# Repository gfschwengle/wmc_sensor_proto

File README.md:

# wmc_sensor_proto
This repo contains everyhting about the project:
- PCB_design: KiCad board design
- firmware: PlatformIO firmware design
- docs: datasheet and images

Still to do;
1. Calibrate the sensor, use a reference sensor. (not tested, atm no reference sensor).
2. Test the system MQTT, to communicate with a raspberry PI (not tested)
3. SD card read and write (Tested, failed)

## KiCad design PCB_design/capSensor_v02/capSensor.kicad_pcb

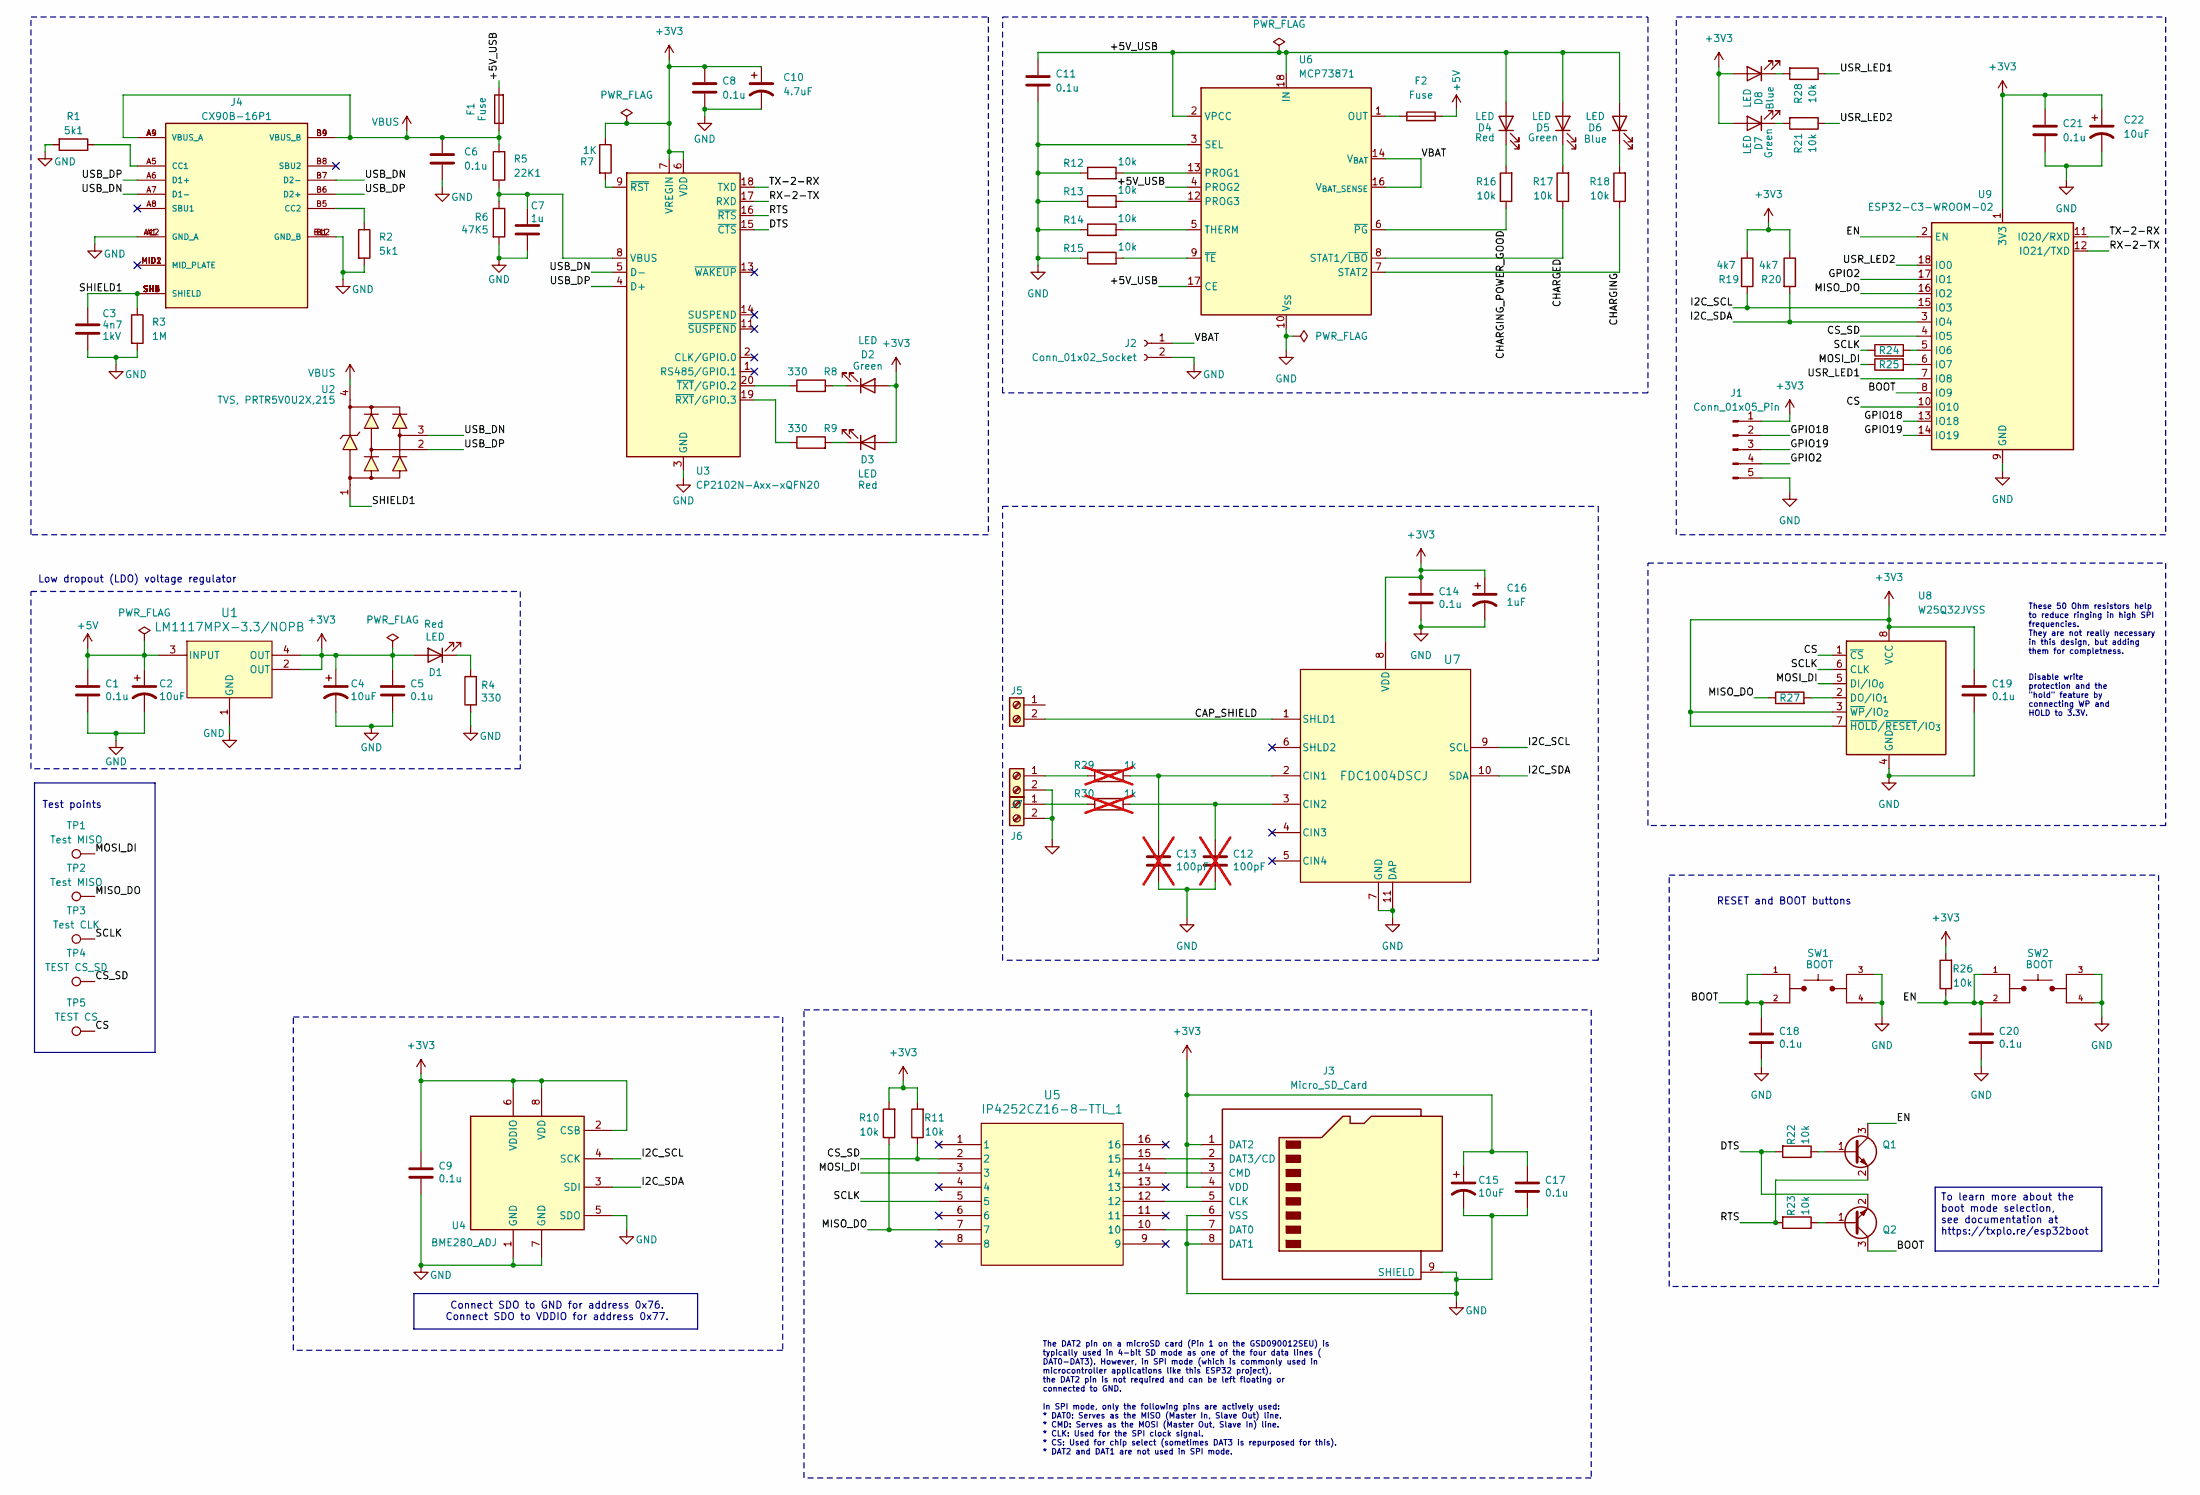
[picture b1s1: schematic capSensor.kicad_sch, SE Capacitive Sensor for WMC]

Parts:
C1, C5, C6, C8, C9, C11, C14, C17, C18, C19, C20, C21: 0.1u; C_0805_2012Metric_Pad1.18x1.45mm_HandSolder; MPN C0805C104K4RACAUTO
C2, C4, C15, C22: 10uF; CAPC3216X110N; MPN T491A106K010AT7280
C3: 4n7; C_0805_2012Metric_Pad1.18x1.45mm_HandSolder; MPN C0805C472K5RECAUTO
C7: 1u; C_0805_2012Metric_Pad1.18x1.45mm_HandSolder; Voltage 1kV; Tolerance 100%; MPN C0805C105K4RACTU
C10: 4.7uF; CAPC3216X110N; MPN T491A475K025AT
C12, C13: 100pF; C_0805_2012Metric_Pad1.18x1.45mm_HandSolder; not fitted
C16: 1uF; CAPC3216X110N; MPN T491A105K016AT
D1, D3, D4: LED; LED_0805_2012Metric_Pad1.15x1.40mm_HandSolder; MPN LTST-C170KRKT
D2, D5, D7: LED; LED_0805_2012Metric_Pad1.15x1.40mm_HandSolder; MPN LTST-C170GKT
D6, D8: LED; LED_0805_2012Metric_Pad1.15x1.40mm_HandSolder; MPN LTST-C170TBKT
F1: Fuse; Fuse_1210_3225Metric_Pad1.42x2.65mm_HandSolder; MPN 0ZCH0110AF2E
F2: Fuse; Fuse_0805_2012Metric_Pad1.15x1.40mm_HandSolder; MPN FBMJ2125HM330-T
J1: Conn_01x05_Pin; PinHeader_1x05_P1.00mm_Vertical_SMD_Pin1Left
J2: Conn_01x02_Socket; JST_S2B-PH-SM4-TB; MPN S2B-PH-SM4-TB
J3: Micro_SD_Card; microSD_HC_Wuerth_693072010801; MPN 693072010801
J4: CX90B-16P1; HIROSE_CX90B-16P1; PARTREV 23.04.05
J5, J6, J7: Screw_Terminal_01x02; TerminalBlock_Xinya_XY308-2.54-2P_1x02_P2.54mm_Horizontal
Q1, Q2: BC817; SOT-23; Manufacturer_Part_Number BC817
R1, R2: 5k1; R_0805_2012Metric_Pad1.20x1.40mm_HandSolder; MPN RMCF0805FT5K10
R3: 1M; R_0805_2012Metric_Pad1.20x1.40mm_HandSolder; MPN RMCF0805FT1M00
R4: 330; R_0805_2012Metric; MPN RMCF0805FT330K
R5: 22K1; R_0805_2012Metric_Pad1.20x1.40mm_HandSolder; MPN RMCF0805FT22K1
R6: 47K5; R_0805_2012Metric; MPN RMCF0805FT47K5
R7: 1K; R_0805_2012Metric_Pad1.20x1.40mm_HandSolder; MPN RNCP0805FTD1K00
R8, R9: 330; R_0805_2012Metric_Pad1.20x1.40mm_HandSolder; MPN RMCF0805FT330K
R10, R11, R12, R13, R14, R15, R16, R17, R18, R21, R22, R23, R26, R28: 10k; R_0805_2012Metric_Pad1.20x1.40mm_HandSolder; MPN RMCF0805FT10K0
R19, R20: 4k7; R_0805_2012Metric_Pad1.20x1.40mm_HandSolder; MPN RMCF0805FT4K70
R24, R25, R27: 50; R_0805_2012Metric; MPN CRCW080550R0FKTA
R29, R30: 1k; R_0805_2012Metric_Pad1.20x1.40mm_HandSolder; not fitted
SW1, SW2: SW_TL3305AF260QG; PARTREV C
TP1, TP2: Test MISO; TestPoint_Pad_D1.0mm
TP3: Test CLK; TestPoint_Pad_D1.0mm
TP4: TEST CS_SD; TestPoint_Pad_D1.0mm
TP5: TEST CS; TestPoint_Pad_D1.0mm
U1: LM1117MPX-3.3/NOPB; DCY0004A_M
U2: TVS, PRTR5V0U2X,215; SOT-143; Voltage - reverse Stand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 5.5V; Voltage - breakdown 6V; MPN PRTR5V0U2X,215; LCSC C12333
U3: CP2102N-Axx-xQFN20; SiliconLabs_QFN-20-1EP_3x3mm_P0.5mm_EP1.8x1.8mm; MPN CP2102N-A02-GQFN20
U4: BME280_ADJ; Bosch_LGA-8_2.5x2.5mm_P0.65mm_ClockwisePinNumbering; MPN BME280
U5: IP4252CZ16-8-TTL_1; QFN16_SOT1168-1_NEX; MPN IP4252CZ16-8-TTL,1
U6: MCP73871; QFN-20-1EP_4x4mm_P0.5mm_EP2.5x2.5mm; MPN MCP73871T-2CCI/ML
U7: FDC1004DSCJ; DSC0010B
U8: W25Q32JVSS; SOIC-8_5.3x5.3mm_P1.27mm; MPN W25Q32JVSSIQ
U9: ESP32-C3-WROOM-02; MPN ESP32-C3-WROOM-02-H4

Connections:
+3V3: C4.1, C5.1, C8.1, C9.1, C10.1, C14.1, C15.1, C16.1, C17.1, C19.1, C21.1, C22.1, D1.2 (A), D2.2 (A), D3.2 (A), D7.2 (A), D8.2 (A), J1.1, J3.1 (DAT2), J3.4 (VDD), R7.1, R10.2, R11.2, R19.1, R20.1, R26.2, U1.2 (OUT), U1.4 (OUT), U3.6 (VDD), U3.7 (VREGIN), U4.2 (CSB), U4.6 (VDDIO), U4.8 (VDD), U7.8 (VDD), U8.3 (~WP/IO_{2}), U8.7 (~HOLD/~RESET/IO_{3}), U8.8 (VCC), U9.1 (3V3)
+5V: C1.1, C2.1, F2.2, U1.3 (INPUT)
/+5V_USB: C11.1, D4.2 (A), D5.2 (A), D6.2 (A), F1.2, U6.2 (VPCC), U6.4 (PROG2), U6.17 (CE), U6.18 (IN), U6.19 (IN)
/BOOT: C18.1, Q2.3 (C), SW1.1, SW1.2, U9.8 (IO9); also elsewhere on the board
/CAP_SHIELD: J5.2, U7.1 (SHLD1)
/CHARGED: R17.1, U6.8 (STAT1/~LBO)
/CHARGING: R18.1, U6.7 (STAT2)
/CHARGING_POWER_GOOD: R16.1, U6.6 (~PG)
/CS: TP5.1, U8.1 (~CS), U9.10 (IO10)
/CS_SD: R11.1, TP4.1, U5.2, U9.4 (IO5)
/DTS: Q2.2 (E), R22.2, U3.15 (~CTS)
/EN: C20.1, Q1.3 (C), R26.1, SW2.1, SW2.2, U9.2 (EN); also elsewhere on the board
/GPIO2: J1.4, U9.17 (IO1)
/GPIO18: J1.2, U9.13 (IO18)
/GPIO19: J1.3, U9.14 (IO19)
/I2C_SCL: R19.2, U4.4 (SCK), U7.9 (SCL), U9.15 (IO3)
/I2C_SDA: R20.2, U4.3 (SDI), U7.10 (SDA), U9.3 (IO4)
/MISO_DO: R10.1, R27.1, TP2.1, U5.7, U9.16 (IO2)
/MOSI_DI: R25.1, TP1.1, U5.3, U8.5 (DI/IO_{0})
/RTS: Q1.2 (E), R23.2, U3.16 (~RTS)
/RX-2-TX: U3.17 (RXD), U9.12 (IO21/TXD)
/SCLK: R24.1, TP3.1, U5.5, U8.6 (CLK)
/SHIELD1: C3.1, J4.SH1 (SHIELD), J4.SH2 (SHIELD), J4.SH3 (SHIELD), J4.SH4 (SHIELD), J4.SH5 (SHIELD), J4.SH6 (SHIELD), R3.1, U2.1
/TX-2-RX: U3.18 (TXD), U9.11 (IO20/RXD)
/USB_DN: J4.A7 (D1-), J4.B7 (D2-), U2.3, U3.5 (D-)
/USB_DP: J4.A6 (D1+), J4.B6 (D2+), U2.2, U3.4 (D+)
/USR_LED1: R28.1, U9.7 (IO8)
/USR_LED2: R21.1, U9.18 (IO0)
/VBAT: J2.1, U6.14 (V_{BAT}), U6.15 (V_{BAT}), U6.16 (V_{BAT_SENSE})
GND: C1.2, C2.2, C3.2, C4.2, C5.2, C6.1, C7.2, C8.2, C9.2, C10.2, C11.2, C12.2, C13.2, C14.2, C15.2, C16.2, C17.2, C18.2, C19.2, C20.2, C21.2, C22.2, J1.5, J2.2, J3.6 (VSS), J3.8 (DAT1), J3.9 (SHIELD), J4.A1 (GND_A), J4.A12 (GND_A), J4.B1 (GND_B), J4.B12 (GND_B), J6.2, J7.2, R1.2, R2.2, R3.2, R4.1, R6.2, R12.1, R13.1, R14.1, R15.1, SW1.3, SW1.4, SW2.3, SW2.4, U1.1 (GND), U3.3 (GND), U3.12 (GND), U3.21 (GND), U4.1 (GND), U4.5 (SDO), U4.7 (GND), U6.3 (SEL), U6.10 (V_{SS}), U6.11 (V_{SS}), U6.21 (V_{SS}), U7.7 (GND), U7.11 (DAP), U7.V, U8.4 (GND), U9.9 (GND), U9.19 (GND); also elsewhere on the board
unnamed: D1.1 (K), R4.2
unnamed: D2.1 (K), R8.2
unnamed: D3.1 (K), R9.2
unnamed: D4.1 (K), R16.2
unnamed: D5.1 (K), R17.2
unnamed: D6.1 (K), R18.2
unnamed: D7.1 (K), R21.2
unnamed: D8.1 (K), R28.2
unnamed: F2.1, U6.1 (OUT), U6.20 (OUT)
unnamed: J3.5 (CLK), U5.12
unnamed: J3.3 (CMD), U5.14
unnamed: J3.7 (DAT0), U5.10
unnamed: J3.2 (DAT3/CD), U5.15
unnamed: J4.A5 (CC1), R1.1
unnamed: J4.B5 (CC2), R2.1
unnamed: J6.1, R30.2
unnamed: J7.1, R29.2
unnamed: Q1.1 (B), R22.1
unnamed: Q2.1 (B), R23.1
unnamed: C7.1, R5.2, R6.1, U3.8 (VBUS)
unnamed: R7.2, U3.9 (~RST)
unnamed: R9.1, U3.19 (~RXT/GPIO.3)
unnamed: R8.1, U3.20 (~TXT/GPIO.2)
unnamed: R12.2, U6.13 (PROG1)
unnamed: R13.2, U6.12 (PROG3)
unnamed: R14.2, U6.5 (THERM)
unnamed: R15.2, U6.9 (~TE)
unnamed: C13.1, R29.1, U7.2 (CIN1)
unnamed: C12.1, R30.1, U7.3 (CIN2)
unnamed: R27.2, U8.2 (DO/IO_{1})
unnamed: R24.2, U9.5 (IO6)
unnamed: R25.2, U9.6 (IO7)
VBUS: C6.2, F1.1, J4.A4 (VBUS_A), J4.A9 (VBUS_A), J4.B4 (VBUS_B), J4.B9 (VBUS_B), R5.1, U2.4

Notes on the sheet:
RESET and BOOT buttons
Low dropout (LDO) voltage regulator
Connect SDO to GND for address 0x76. Connect SDO to VDDIO for address 0x77.
Test points
These 50 Ohm resistors help to reduce ringing in high SPI frequencies. They are not really necessary in this design, but adding them for completness.
Disable write protection and the "hold" feature by connecting WP and HOLD to 3.3V.
To learn more about the boot mode selection, see documentation at https://txplo.re/esp32boot
The DAT2 pin on a microSD card (Pin 1 on the GSD090012SEU) is typically used in 4-bit SD mode as one of the four data lines ( DAT0-DAT3). However, in SPI mode (which is commonly used in microcontroller applications like this ESP32 project), the DAT2 pin is not required and can be left floating or c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

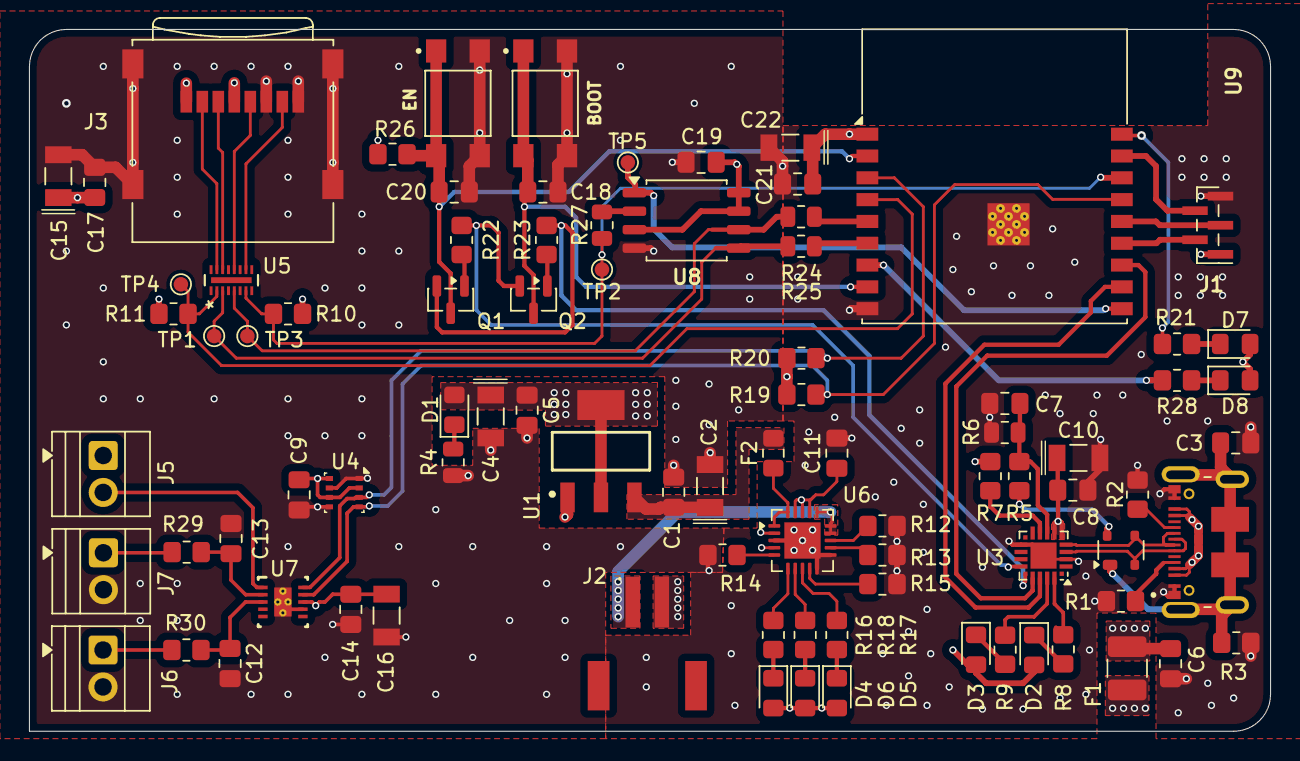
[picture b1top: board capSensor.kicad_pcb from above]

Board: 4 copper layers, 85.3 x 48.3 mm, 87 parts (0 on the bottom side), 63 nets.

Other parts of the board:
BOOT: SW_TL3305AF260QG
EN: SW_TL3305AF260QG

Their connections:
/BOOT: BOOT.1, BOOT.2; also elsewhere on the board
/EN: EN.1, EN.2; also elsewhere on the board
GND: BOOT.3, BOOT.4, EN.3, EN.4; also elsewhere on the board

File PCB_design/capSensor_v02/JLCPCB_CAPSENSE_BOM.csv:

Reference,Qty,Value,DNP,Footprint,LCSC
"C1,C5,C6,C8,C9,C11,C14,C17,C18,C19,C20,C21",12,0.1u,,Capacitor_SMD:C_0805_2012Metric_Pad1.18x1.45mm_HandSolder,C1845706
"C2,C4,C15,C22",4,10uF,,schwengle-electronics:CAPC3216X110N,C1954014
C3,1,4n7,,Capacitor_SMD:C_0805_2012Metric_Pad1.18x1.45mm_HandSolder,C2170406
C7,1,1u,,Capacitor_SMD:C_0805_2012Metric_Pad1.18x1.45mm_HandSolder,C2167376
C10,1,4.7uF,,schwengle-electronics:CAPC3216X110N,C118128
"C12,C13",2,100pF,DNP,Capacitor_SMD:C_0805_2012Metric_Pad1.18x1.45mm_HandSolder,
C16,1,1uF,,schwengle-electronics:CAPC3216X110N,C116269
"D1, D3, D4",3,LED RED,,LED_SMD:LED_0805_2012Metric_Pad1.15x1.40mm_HandSolder,C94868
"D2, D5, D7",3,LED Green,,LED_SMD:LED_0805_2012Metric_Pad1.15x1.40mm_HandSolder,C125090
"D6, D8",2,LED BLUE,,LED_SMD:LED_0805_2012Metric_Pad1.15x1.40mm_HandSolder,C98222
F1,1,Fuse,,Fuse:Fuse_1210_3225Metric_Pad1.42x2.65mm_HandSolder,C3762512
F2,1,Fuse,,Fuse:Fuse_0805_2012Metric_Pad1.15x1.40mm_HandSolder,C271757
J1,1,Conn_01x05_Pin,,Connector_PinHeader_1.00mm:PinHeader_1x05_P1.00mm_Vertical_SMD_Pin1Left,C7127982
J2,1,Conn_01x02_Socket,,schwengle-electronics:JST_S2B-PH-SM4-TB,C295747
J3,1,Micro_SD_Card Wurth 693072010801,,Connector_Card:microSD_HC_Wuerth_693072010801,
J4,1,CX90B-16P1,,schwengle-electronics:HIROSE_CX90B-16P1,C3198004
"J5,J6,J7",3,Screw_Terminal_01x02,,TerminalBlock:TerminalBlock_Xinya_XY308-2.54-2P_1x02_P2.54mm_Horizontal,C592983
"Q1,Q2",2,BC817,,Package_TO_SOT_SMD:SOT-23,C554103
"R1,R2",2,5k1,,Resistor_SMD:R_0805_2012Metric_Pad1.20x1.40mm_HandSolder,C2479694
R3,1,1M,,Resistor_SMD:R_0805_2012Metric_Pad1.20x1.40mm_HandSolder,C2479714
R4,1,330,,Resistor_SMD:R_0805_2012Metric,C2479639
R5,1,22K1,,Resistor_SMD:R_0805_2012Metric_Pad1.20x1.40mm_HandSolder,C2479697
R6,1,47K5,,Resistor_SMD:R_0805_2012Metric,C3971326
R7,1,1K,,Resistor_SMD:R_0805_2012Metric_Pad1.20x1.40mm_HandSolder,C2441430
"R8,R9",2,330,,Resistor_SMD:R_0805_2012Metric_Pad1.20x1.40mm_HandSolder,C2479639
"R10,R11,R12,R13,R14,R15,R16,R17,R18,R21,R22,R23,R26,R28",14,10k,,Resistor_SMD:R_0805_2012Metric_Pad1.20x1.40mm_HandSolder,C237755
"R19,R20",2,4k7,,Resistor_SMD:R_0805_2012Metric_Pad1.20x1.40mm_HandSolder,C2479702
"R24,R25,R27",3,50,,Resistor_SMD:R_0805_2012Metric,C4179671
"R29,R30",2,1k,DNP,Resistor_SMD:R_0805_2012Metric_Pad1.20x1.40mm_HandSolder,
"SW1,SW2",2,TL3305AF260QG,,schwengle-electronics:SW_TL3305AF260QG,C2886902
"TP1,TP2",2,Test MISO,,TestPoint:TestPoint_Pad_D1.0mm,
TP3,1,Test CLK,,TestPoint:TestPoint_Pad_D1.0mm,
TP4,1,TEST CS_SD,,TestPoint:TestPoint_Pad_D1.0mm,
TP5,1,TEST CS,,TestPoint:TestPoint_Pad_D1.0mm,
U1,1,LM1117MPX-3.3/NOPB,,schwengle-electronics:DCY0004A_M,C9662
U2,1,"TVS, PRTR5V0U2X,215",,Package_TO_SOT_SMD:SOT-143,C12333
U3,1,CP2102N-Axx-xQFN20,,Package_DFN_QFN:SiliconLabs_QFN-20-1EP_3x3mm_P0.5mm_EP1.8x1.8mm,C969913
U4,1,BME280_ADJ,,Package_LGA:Bosch_LGA-8_2.5x2.5mm_P0.65mm_ClockwisePinNumbering,C92489
U5,1,IP4252CZ16-8-TTL_1,,IP4252CZ16_8_TTL_1:QFN16_SOT1168-1_NEX,C458218
U6,1,MCP73871,,Package_DFN_QFN:QFN-20-1EP_4x4mm_P0.5mm_EP2.5x2.5mm,C511310
U7,1,FDC1004DSCJ,,FDC1004:DSC0010B,C2652081
U8,1,W25Q32JVSS,,Package_SO:SOIC-8_5.3x5.3mm_P1.27mm,C179173
U9,1,ESP32-C3-WROOM-02,,RF_Module:ESP32-C3-WROOM-02,C2944070

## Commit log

2026-01-18 Initial plan
2026-01-18 Create complete capsensor_hva repository structure with documentation
2026-01-18 Address code review feedback: clean up .gitignore and fix PlatformIO setup instructions
2026-01-18 Fix PlatformIO installation command and clean up platformio.ini formatting
2026-01-18 Create capsensor_hva project structure with firmware, hardware, and documentation
2026-01-18 Create PCB_design
2026-01-18 Create hello
2026-01-18 Revise README for comprehensive project documentation
    Expanded README with detailed project overview, features, hardware platform, GPIO configuration, project architecture, configuration instructions, build and upload steps, troubleshooting tips, known 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
2026-01-18 Revise README with project details and tasks
    Updated project description and added to-do list.
